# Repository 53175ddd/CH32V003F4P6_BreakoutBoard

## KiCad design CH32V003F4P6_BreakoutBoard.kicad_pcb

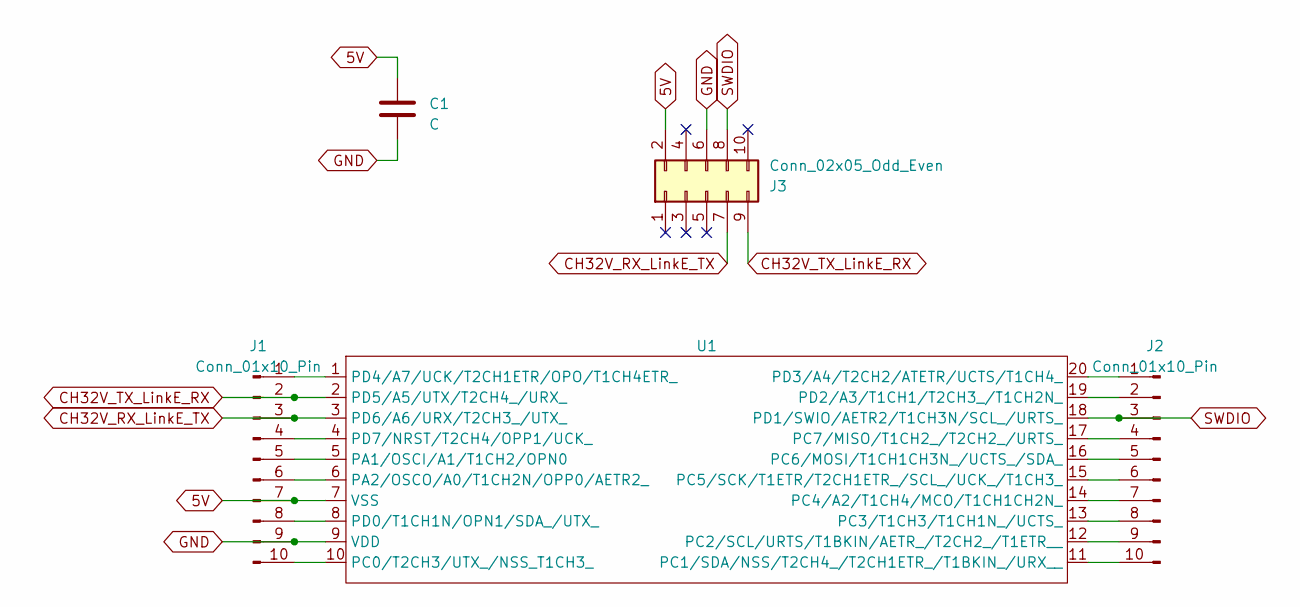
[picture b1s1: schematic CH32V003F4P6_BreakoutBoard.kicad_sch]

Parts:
C1: C; C_0603_1608Metric
J1, J2: Conn_01x10_Pin; PinHeader_1x10_P2.54mm_Vertical
J3: Conn_02x05_Odd_Even; PinHeader_2x05_P2.54mm_Vertical
U1: SSOP-20_4.4x6.5mm_P0.65mm

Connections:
5V: C1.1, J1.7, J3.2, U1.7 (VSS)
CH32V_RX_LinkE_TX: J1.3, J3.7, U1.3 (PD6/A6/URX/T2CH3_/UTX_)
CH32V_TX_LinkE_RX: J1.2, J3.9, U1.2 (PD5/A5/UTX/T2CH4_/URX_)
GND: C1.2, J1.9, J3.6, U1.9 (VDD)
unnamed: J1.1, U1.1 (PD4/A7/UCK/T2CH1ETR/OPO/T1CH4ETR_)
unnamed: J1.4, U1.4 (PD7/NRST/T2CH4/OPP1/UCK_)
unnamed: J1.5, U1.5 (PA1/OSCI/A1/T1CH2/OPN0)
unnamed: J1.6, U1.6 (PA2/OSCO/A0/T1CH2N/OPP0/AETR2_)
unnamed: J1.8, U1.8 (PD0/T1CH1N/OPN1/SDA_/UTX_)
unnamed: J1.10, U1.10 (PC0/T2CH3/UTX_/NSS_T1CH3_)
unnamed: J2.1, U1.20 (PD3/A4/T2CH2/ATETR/UCTS/T1CH4_)
unnamed: J2.2, U1.19 (PD2/A3/T1CH1/T2CH3_/T1CH2N_)
unnamed: J2.4, U1.17 (PC7/MISO/T1CH2_/T2CH2_/URTS_)
unnamed: J2.5, U1.16 (PC6/MOSI/T1CH1CH3N_/UCTS_/SDA_)
unnamed: J2.6, U1.15 (PC5/SCK/T1ETR/T2CH1ETR_/SCL_/UCK_/T1CH3_)
unnamed: J2.7, U1.14 (PC4/A2/T1CH4/MCO/T1CH1CH2N_)
unnamed: J2.8, U1.13 (PC3/T1CH3/T1CH1N_/UCTS_)
unnamed: J2.9, U1.12 (PC2/SCL/URTS/T1BKIN/AETR_/T2CH2_/T1ETR__)
unnamed: J2.10, U1.11 (PC1/SDA/NSS/T2CH4_/T2CH1ETR_/T1BKIN_/UR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)
SWDIO: J2.3, J3.8, U1.18 (PD1/SWIO/AETR2/T1CH3N/SCL_/URTS_)

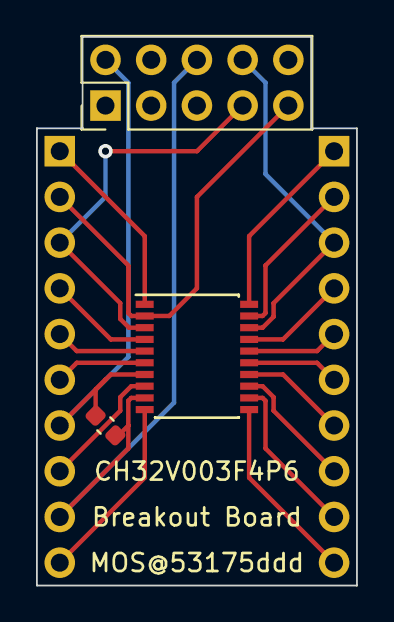
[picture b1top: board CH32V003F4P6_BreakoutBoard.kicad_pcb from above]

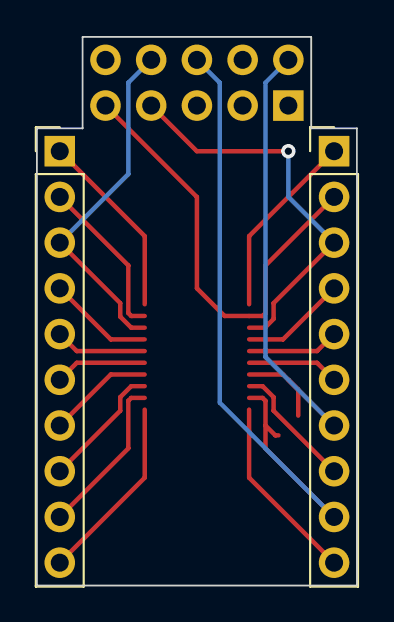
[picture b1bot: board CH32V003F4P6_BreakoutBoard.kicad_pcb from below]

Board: 2 copper layers, 17.8 x 30.5 mm, 5 parts (2 on the bottom side), 20 nets.
